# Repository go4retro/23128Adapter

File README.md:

# 23128Adapter
MOS 23128 to JEDEC 27XX(X) Adapter

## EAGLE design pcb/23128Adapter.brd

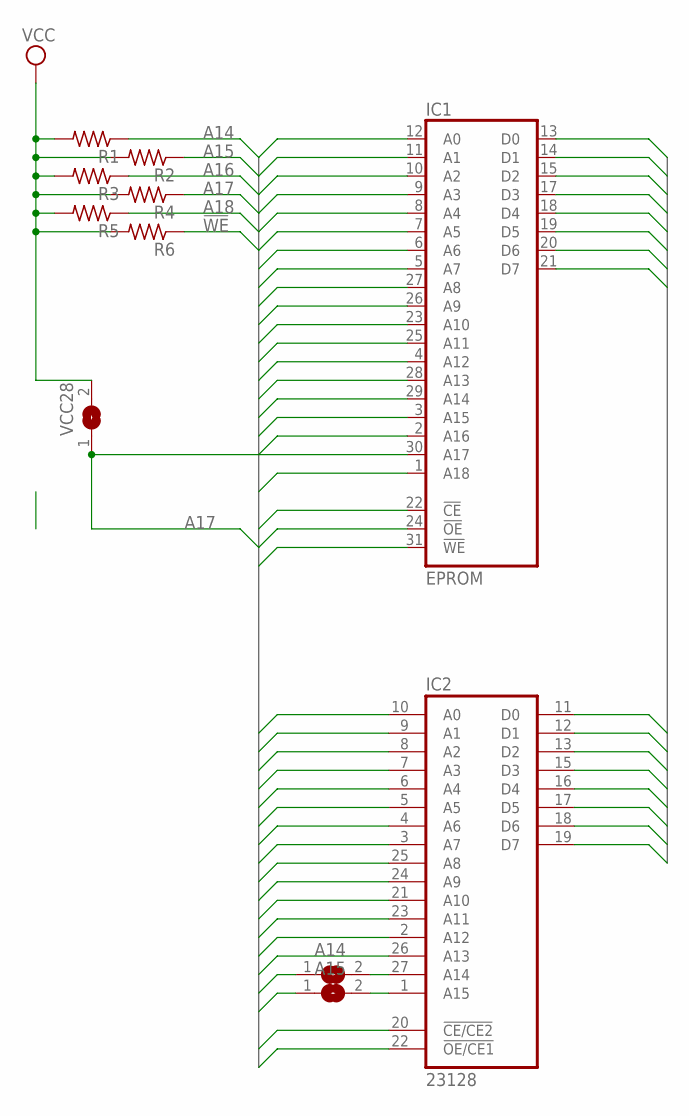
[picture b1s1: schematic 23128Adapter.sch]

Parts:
A14, A15: SJ
IC1: EPROM; DIL32-6ROUNDPAD
IC2: 23128; DIL28-ROUNDPAD
R1, R2, R3, R4, R5, R6: R-US_0204/5; 0204/5
VCC28: SJ

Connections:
!CE: IC1.22 (!CE), IC2.20 (!CE/CE2)
!OE: IC1.24 (!OE), IC2.22 (!OE/CE1)
!WE: IC1.31 (!WE), R6.1
A0: IC1.12 (A0), IC2.10 (A0)
A1: IC1.11 (A1), IC2.9 (A1)
A2: IC1.10 (A2), IC2.8 (A2)
A3: IC1.9 (A3), IC2.7 (A3)
A4: IC1.8 (A4), IC2.6 (A4)
A5: IC1.7 (A5), IC2.5 (A5)
A6: IC1.6 (A6), IC2.4 (A6)
A7: IC1.5 (A7), IC2.3 (A7)
A8: IC1.27 (A8), IC2.25 (A8)
A9: IC1.26 (A9), IC2.24 (A9)
A10: IC1.23 (A10), IC2.21 (A10)
A11: IC1.25 (A11), IC2.23 (A11)
A12: IC1.4 (A12), IC2.2 (A12)
A13: IC1.28 (A13), IC2.26 (A13)
A14: A14.1, IC1.29 (A14), R1.1
A15: A15.1, IC1.3 (A15), R2.1
A16: IC1.2 (A16), R3.1
A17: IC1.30 (A17), R4.1, VCC28.1
A18: IC1.1 (A18), R5.1
D0: IC1.13 (D0), IC2.11 (D0)
D1: IC1.14 (D1), IC2.12 (D1)
D2: IC1.15 (D2), IC2.13 (D2)
D3: IC1.17 (D3), IC2.15 (D3)
D4: IC1.18 (D4), IC2.16 (D4)
D5: IC1.19 (D5), IC2.17 (D5)
D6: IC1.20 (D6), IC2.18 (D6)
D7: IC1.21 (D7), IC2.19 (D7)
GND: IC1.16 (GND), IC2.14 (GND)
unnamed: A14.2, IC2.27 (A14)
unnamed: A15.2, IC2.1 (A15)
VCC: IC1.32 (VCC), IC2.28 (VCC), R1.2, R2.2, R3.2, R4.2, R5.2, R6.2, VCC28.2

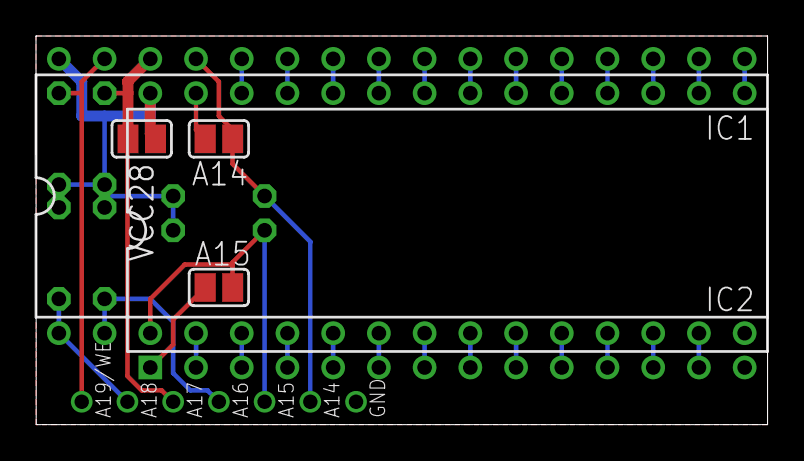
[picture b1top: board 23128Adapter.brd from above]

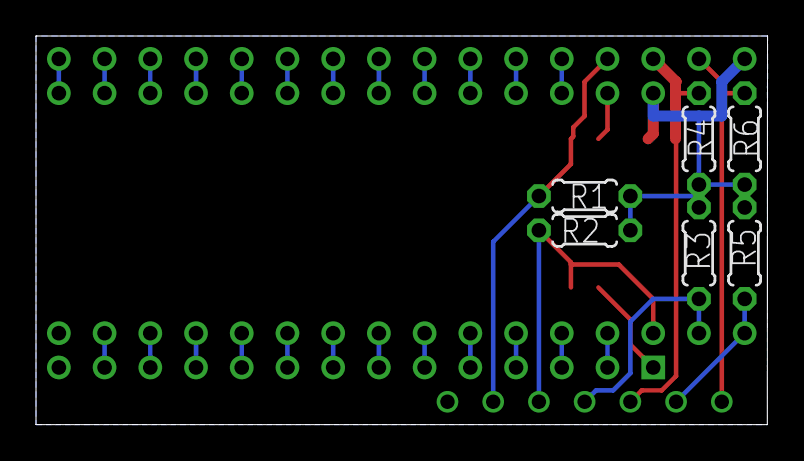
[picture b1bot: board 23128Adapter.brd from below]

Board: 2 copper layers, 40.6 x 21.6 mm, 11 parts (6 on the bottom side), 34 nets.

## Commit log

2018-03-11 Updated license
2018-03-11 Added README.md
2020-10-11 PCB Updates

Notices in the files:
pcb/23128Adapter.brd:
(c) 2014 RETRO Innovations
